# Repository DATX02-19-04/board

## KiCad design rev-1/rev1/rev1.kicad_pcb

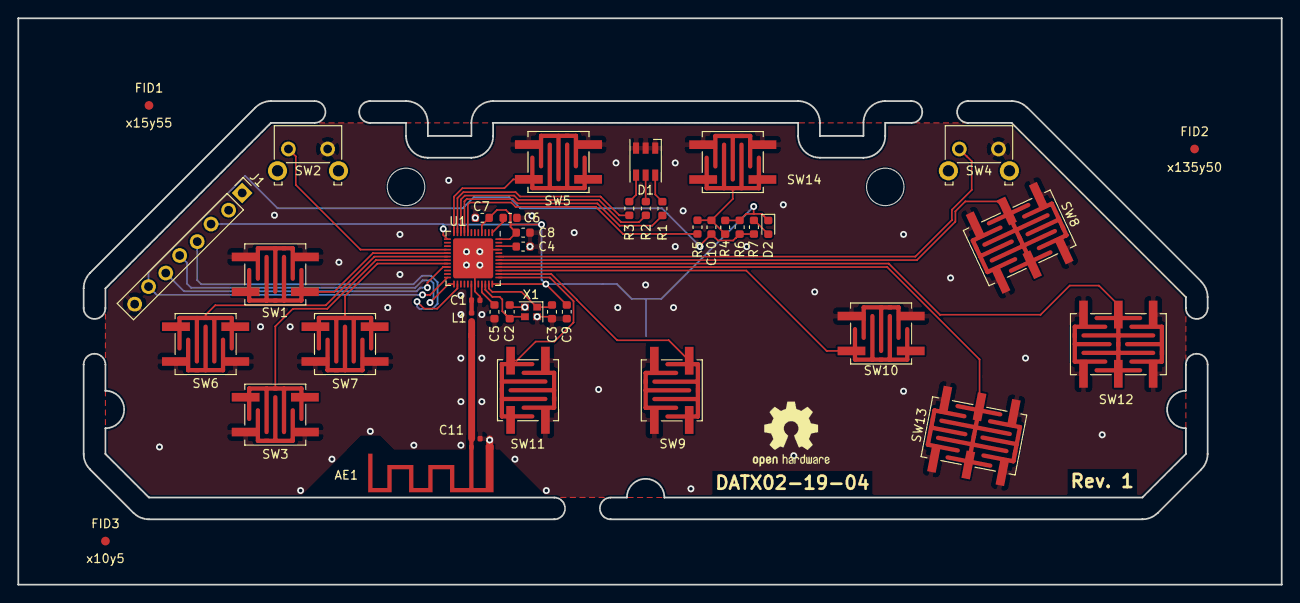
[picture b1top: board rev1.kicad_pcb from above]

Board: 2 copper layers, 145.0 x 65.0 mm, 43 parts (1 on the bottom side), 35 nets.

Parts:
AE1: Antenna_Shield; Texas_SWRA117D_2.4GHz_Right_MOD
BT1: Battery_Cell; S8421-45R
C1: 0.8pF; C_0402_1005Metric
C2, C3: 12pF; C_0603_1608Metric
C4: 1uF; C_0603_1608Metric
C5: 100pF; C_0603_1608Metric
C6, C7, C8: 100nF; C_0603_1608Metric
C9: 4.7u; C_0603_1608Metric
C10: 100n; C_0603_1608Metric
C11: C; C_0402_1005Metric
D1: LED_RGB; LED_RGB_PLCC-6
D2: D; D_0603_1608Metric
FID1: x15y55; Fiducial_1mm_Mask2mm
FID2: x135y50; Fiducial_1mm_Mask2mm
FID3: x10y5; Fiducial_1mm_Mask2mm
J1: Conn_01x08_Female; PinHeader_1x08_P2.54mm_Staggered
L1: 3.9nH; L_0402_1005Metric
R1, R2, R3: R; R_0603_1608Metric
R4, R5: 10k; R_0603_1608Metric
R6: 100k; R_0603_1608Metric
R7: 100R; R_0603_1608Metric
SW1: DPAD_UP; SW_SPST_EVQQ2_RUBBERDOME_NORMAL
SW2: BTN_L; SW_Tactile_SKHH_Angled_Fixed
SW3: DPAD_DOWN; SW_SPST_EVQQ2_RUBBERDOME_NORMAL
SW4: BTN_R; SW_Tactile_SKHH_Angled_Fixed
SW5: BTN_BLUTOOTH; SW_SPST_EVQQ2_RUBBERDOME_NORMAL
SW6: DPAD_LEFT; SW_SPST_EVQQ2_RUBBERDOME_NORMAL
SW7: DPAD_RIGHT; SW_SPST_EVQQ2_RUBBERDOME_NORMAL
SW8: BTN_X; SW_SPST_EVQQ2_RUBBERDOME_DOUBLE
SW9: BTN_START; SW_SPST_EVQQ2_RUBBERDOME_NORMAL
SW10: BTN_Y; SW_SPST_EVQQ2_RUBBERDOME_NORMAL
SW11: BTN_SELECT; SW_SPST_EVQQ2_RUBBERDOME_NORMAL
SW12: BTN_A; SW_SPST_EVQQ2_RUBBERDOME_DOUBLE
SW13: BTN_B; SW_SPST_EVQQ2_RUBBERDOME_DOUBLE
SW14: RESET; SW_SPST_EVQQ2_RUBBERDOME_NORMAL
U1: nRF52810-QFxx; QFN-48-1EP_6x6mm_P0.4mm_EP4.6x4.6mm
X1: 32MHz; Crystal_SMD_2016-4Pin_2.0x1.6mm

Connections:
/BTN_A: SW12.1, U1.41
/BTN_B: SW13.1, U1.40
/BTN_BLUETOOTH: SW5.1, U1.12
/BTN_L: SW2.1, U1.16
/BTN_R: SW4.1, U1.43
/BTN_SELECT: SW11.1, U1.37
/BTN_START: SW9.1, U1.38
/BTN_X: SW8.1, U1.42
/BTN_Y: SW10.1, U1.39
/DPAD_DOWN: SW3.1, U1.19
/DPAD_LEFT: SW6.1, U1.18
/DPAD_RIGHT: SW7.1, U1.20
/DPAD_UP: SW1.1, U1.17
/LED_B: R3.1, U1.11
/LED_G: R2.1, U1.10
/LED_R: R1.1, U1.9
/P0.18: J1.6, U1.21
/RESET_SENSE: R5.2, U1.8
/SWDCLK: J1.5, U1.25
/SWDIO: J1.4, U1.26
/~RESET: C10.1, J1.7, R6.1, R7.1, U1.24
GND: AE1.2, BT1.2, C1.1, C2.2, C3.2, C4.1, C5.1, C6.2, C7.1, C8.1, C9.1, C11.2, D1.1, D1.2, D1.3, J1.8, SW1.2, SW2.2, SW3.2, SW4.2, SW5.2, SW6.2, SW7.2, SW8.2, SW9.2, SW10.2, SW11.2, SW12.2, SW13.2, SW14.2, U1.31, U1.45, U1.49, X1.2, X1.4
unnamed: AE1.1, C11.1, L1.1
unnamed: C1.2, L1.2, U1.30
unnamed: C2.1, U1.34, X1.3
unnamed: C3.1, U1.35, X1.1
unnamed: C4.2, U1.46
unnamed: C5.2, U1.33
unnamed: C6.1, U1.1
unnamed: C10.2, R4.1, R5.1, SW14.1
unnamed: D1.4, R3.2
unnamed: D1.5, R2.2
unnamed: D1.6, R1.2
unnamed: D2.2, R7.2
VCC: BT1.1, C7.2, C8.2, C9.2, D2.1, J1.3, R4.2, R6.2, U1.4, U1.13, U1.36, U1.48

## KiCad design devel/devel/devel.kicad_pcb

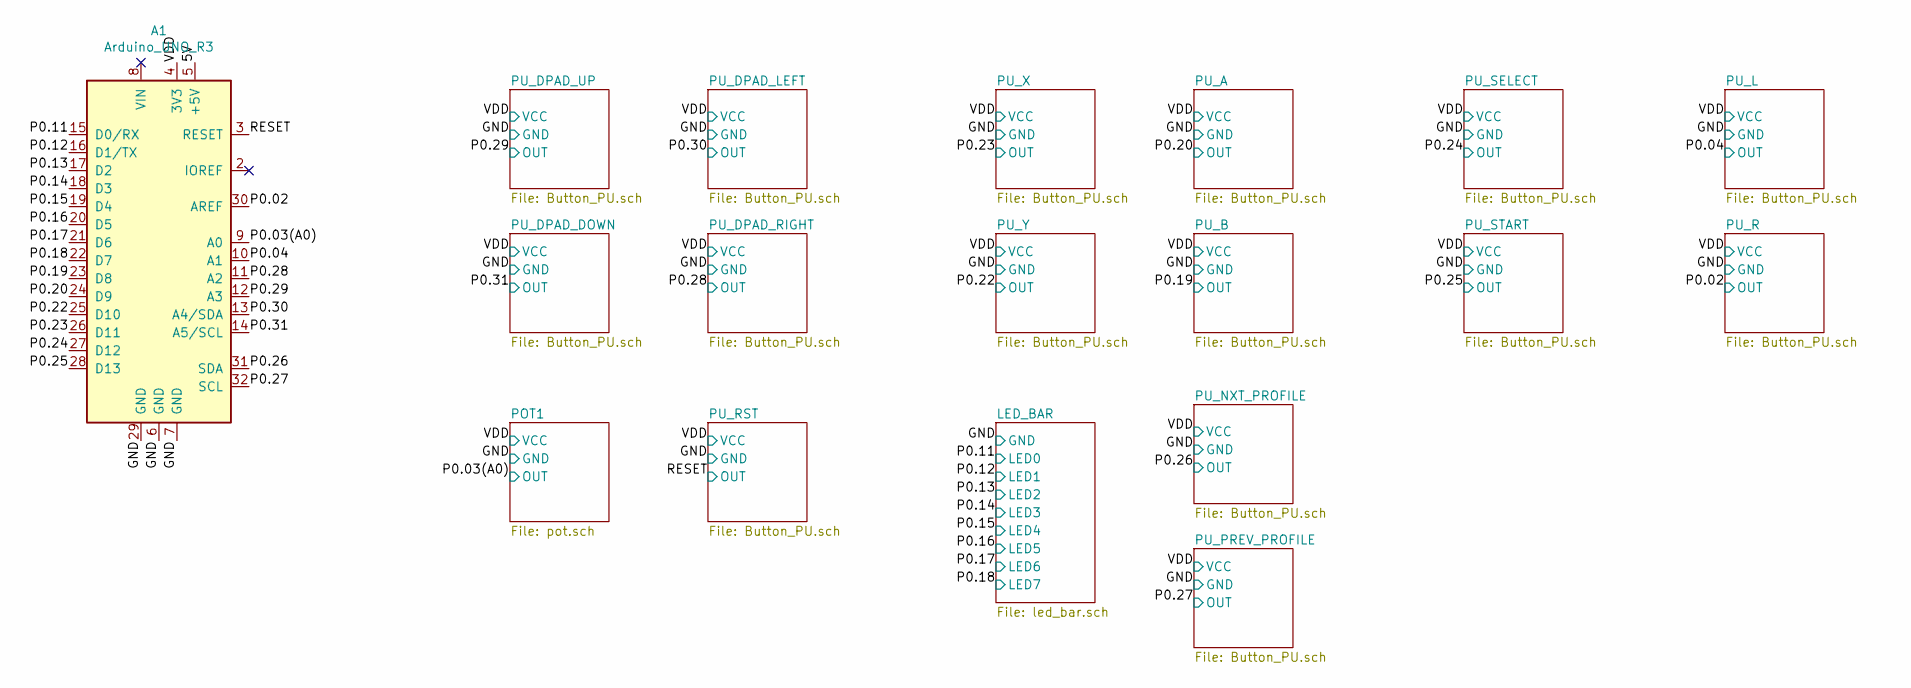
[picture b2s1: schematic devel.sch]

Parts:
A1: Arduino_UNO_R3

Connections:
/GND: A1.6 (GND), A1.7 (GND), A1.29 (GND); also elsewhere on the board
/P0.02: A1.30 (AREF); also elsewhere on the board
/P0.03(A0): A1.9 (A0); also elsewhere on the board
/P0.04: A1.10 (A1); also elsewhere on the board
/P0.11: A1.15 (D0/RX); also elsewhere on the board
/P0.12: A1.16 (D1/TX); also elsewhere on the board
/P0.13: A1.17 (D2); also elsewhere on the board
/P0.14: A1.18 (D3); also elsewhere on the board
/P0.15: A1.19 (D4); also elsewhere on the board
/P0.16: A1.20 (D5); also elsewhere on the board
/P0.17: A1.21 (D6); also elsewhere on the board
/P0.18: A1.22 (D7); also elsewhere on the board
/P0.19: A1.23 (D8); also elsewhere on the board
/P0.20: A1.24 (D9); also elsewhere on the board
/P0.22: A1.25 (D10); also elsewhere on the board
/P0.23: A1.26 (D11); also elsewhere on the board
/P0.24: A1.27 (D12); also elsewhere on the board
/P0.25: A1.28 (D13); also elsewhere on the board
/P0.26: A1.31 (SDA); also elsewhere on the board
/P0.27: A1.32 (SCL); also elsewhere on the board
/P0.28: A1.11 (A2); also elsewhere on the board
/P0.29: A1.12 (A3); also elsewhere on the board
/P0.30: A1.13 (A4/SDA); also elsewhere on the board
/P0.31: A1.14 (A5/SCL); also elsewhere on the board
/RESET: A1.3 (RESET); also elsewhere on the board
/VDD: A1.4 (3V3); also elsewhere on the board

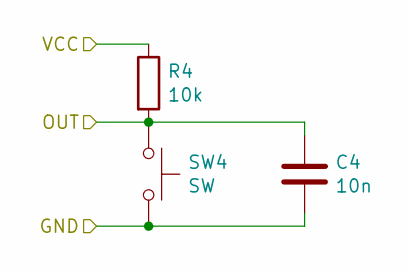
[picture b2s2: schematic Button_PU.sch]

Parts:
C1: 10n; C_0805_2012Metric_Pad1.15x1.40mm_HandSolder
R1: 10k; R_0805_2012Metric_Pad1.15x1.40mm_HandSolder
SW1: SW; SW_SPST_EVQQ2

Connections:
/GND: C1.2, SW1.2; also elsewhere on the board
/P0.28: C1.1, R1.2, SW1.1; also elsewhere on the board
/VDD: R1.1; also elsewhere on the board

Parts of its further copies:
C2, C3, C4, C5, C6, C7, C8, C9, C10, C11, C12, C14, C15, C16: 10n; C_0805_2012Metric_Pad1.15x1.40mm_HandSolder
R2, R3, R4, R5, R6, R7, R8, R9, R10, R11, R12, R13, R14, R23: 10k; R_0805_2012Metric_Pad1.15x1.40mm_HandSolder
SW2, SW3, SW4, SW5, SW6, SW7, SW8, SW9, SW10, SW11, SW12, SW13, SW14, SW15: SW; SW_SPST_EVQQ2

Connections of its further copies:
/GND: C2.2, C3.2, C4.2, C5.2, C6.2, C7.2, C8.2, C9.2, C10.2, C11.2, C12.2, C14.2, C15.2, C16.2, SW2.2, SW3.2, SW4.2, SW5.2, SW6.2, SW7.2, SW8.2, SW9.2, SW10.2, SW11.2, SW12.2, SW13.2, SW14.2, SW15.2; also elsewhere on the board
/P0.02: C5.1, R5.2, SW5.1; also elsewhere on the board
/P0.04: C4.1, R4.2, SW4.1; also elsewhere on the board
/P0.11: C15.1, R14.2, SW14.1; also elsewhere on the board
/P0.12: C14.1, R13.2, SW13.1; also elsewhere on the board
/P0.22: C10.1, R10.2, SW10.1; also elsewhere on the board
/P0.23: C9.1, R9.2, SW9.1; also elsewhere on the board
/P0.24: C6.1, R6.2, SW6.1; also elsewhere on the board
/P0.25: C8.1, R8.2, SW8.1; also elsewhere on the board
/P0.26: C7.1, R7.2, SW7.1; also elsewhere on the board
/P0.27: C12.1, R12.2, SW12.1; also elsewhere on the board
/P0.29: C2.1, R2.2, SW2.1; also elsewhere on the board
/P0.30: C3.1, R3.2, SW3.1; also elsewhere on the board
/P0.31: C11.1, R11.2, SW11.1; also elsewhere on the board
/RESET: C16.1, R23.2, SW15.1; also elsewhere on the board
/VDD: R2.1, R3.1, R4.1, R5.1, R6.1, R7.1, R8.1, R9.1, R10.1, R11.1, R12.1, R13.1, R14.1, R23.1; also elsewhere on the board

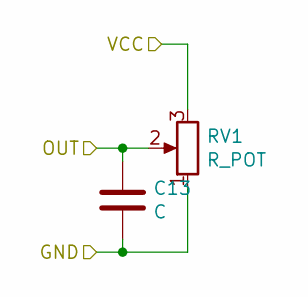
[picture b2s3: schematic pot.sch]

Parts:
C13: C; C_0805_2012Metric_Pad1.15x1.40mm_HandSolder
RV1: R_POT; Potentiometer_Alps_RK163_Single_Horizontal

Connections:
/GND: C13.2, RV1.1; also elsewhere on the board
/P0.03(A0): C13.1, RV1.2; also elsewhere on the board
/VDD: RV1.3; also elsewhere on the board

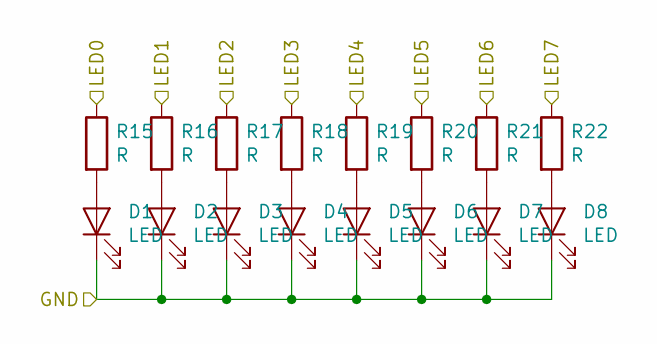
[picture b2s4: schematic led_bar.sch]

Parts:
D1, D2, D3, D4, D5, D6, D7, D8: LED; LED_0603_1608Metric_Pad1.05x0.95mm_HandSolder
R15, R16, R17, R18, R19, R20, R21, R22: R; R_0805_2012Metric_Pad1.15x1.40mm_HandSolder

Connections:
/GND: D1.1 (K), D2.1 (K), D3.1 (K), D4.1 (K), D5.1 (K), D6.1 (K), D7.1 (K), D8.1 (K); also elsewhere on the board
/P0.13: R15.1; also elsewhere on the board
/P0.14: R16.1; also elsewhere on the board
/P0.15: R17.1; also elsewhere on the board
/P0.16: R18.1; also elsewhere on the board
/P0.17: R19.1; also elsewhere on the board
/P0.18: R20.1; also elsewhere on the board
/P0.19: R21.1; also elsewhere on the board
/P0.20: R22.1; also elsewhere on the board
unnamed: D1.2 (A), R15.2
unnamed: D2.2 (A), R16.2
unnamed: D3.2 (A), R17.2
unnamed: D4.2 (A), R18.2
unnamed: D5.2 (A), R19.2
unnamed: D6.2 (A), R20.2
unnamed: D7.2 (A), R21.2
unnamed: D8.2 (A), R22.2

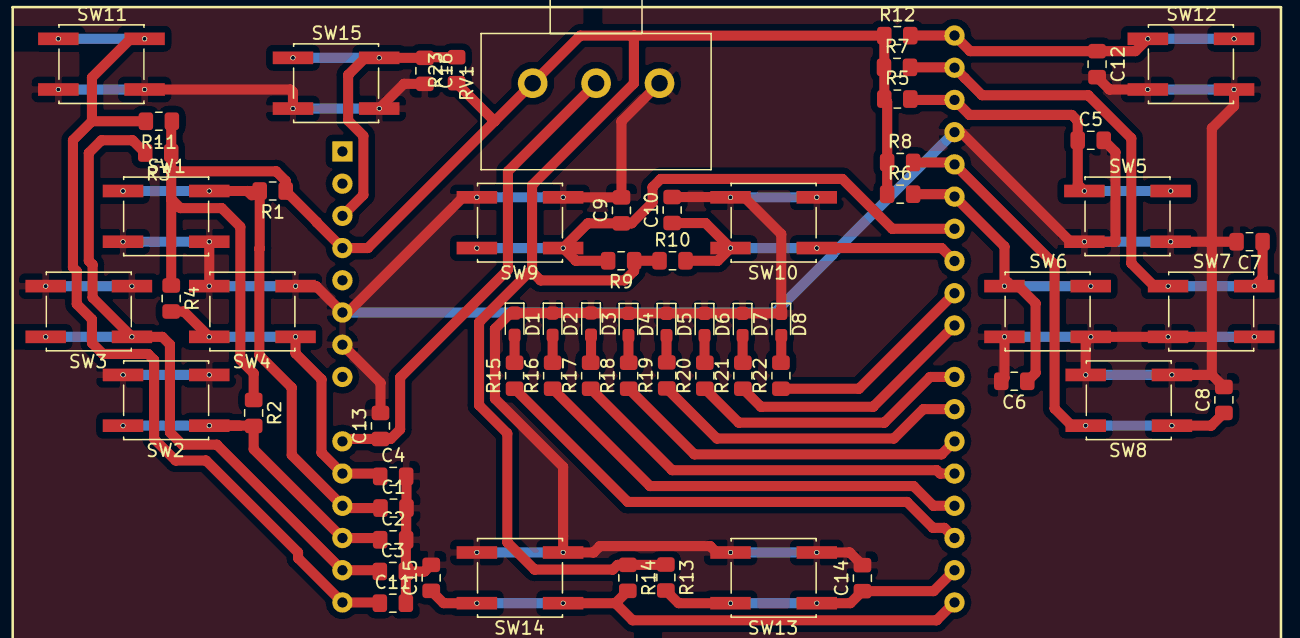
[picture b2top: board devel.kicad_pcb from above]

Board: 2 copper layers, 64 parts (1 on the bottom side), 34 nets.

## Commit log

2019-02-04 Created development board for devboard
2019-02-05 Worked on the dev-board
2019-02-05 Make a physical border
2019-02-05 Preliminary placement and orientation of components to fit the board
2019-02-06 Completed the PCB desing for devel, ready to etch
2019-02-06 Made Gustav's design into a double sided board
2019-03-17 work
2019-03-22 More Work, almost done with rev 1
2019-03-22 More work again
2019-03-25 Rev 1 finished
